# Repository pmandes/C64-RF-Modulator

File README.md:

# C64-RF-Modulator with S-Video Mod

This is a project of a modulator replacement based on an analog c0pperdragon module. It was adjusted in size to the Commodore C64C motherboard and extended with S-Video and Strereo Audio outputs.

### Changelog:

1.2
- internal audio route to left and/or right channel
- ferrite beads to suppresses high-frequency electronic noise
- silkscreen layer with descriptions of all outputs and elements
- 3D models for a nice rendering
- project cleaned up and migrated to KiCad 6.0
- interactive BOM

1.1
- prototype fixes

1.0
- PCB size adjusted to C64C motherboards (ASSY No.250469)
- S-Video connector added (mini-DIN 4)
- added standard stereo audio mini-jack 3.5mm output

### Bill of materials:

<p align="center">

</p>

### Final revision:

- all jumpers removed: audio output from an external source (e.g. MixSID)
- all jumpers on: mono signal from the motherboard connected to the left and right channels

### Prototype images:

The board connected to SixtyClone. Image from S-Video output:

The board can be soldered with pins to the motherboard. Then the S-Video and Audio outputs will be at the level of the corresponding openings in the housing.

### Links:
- c0pperdragon analog module: https://github.com/c0pperdragon/C64-Video-Enhancement/tree/master/analog_only
- order PCBs directly from PCBWay: https://www.pcbway.com/project/shareproject/Commodore_C64C_modulator_replacement_0f6cacf9.html

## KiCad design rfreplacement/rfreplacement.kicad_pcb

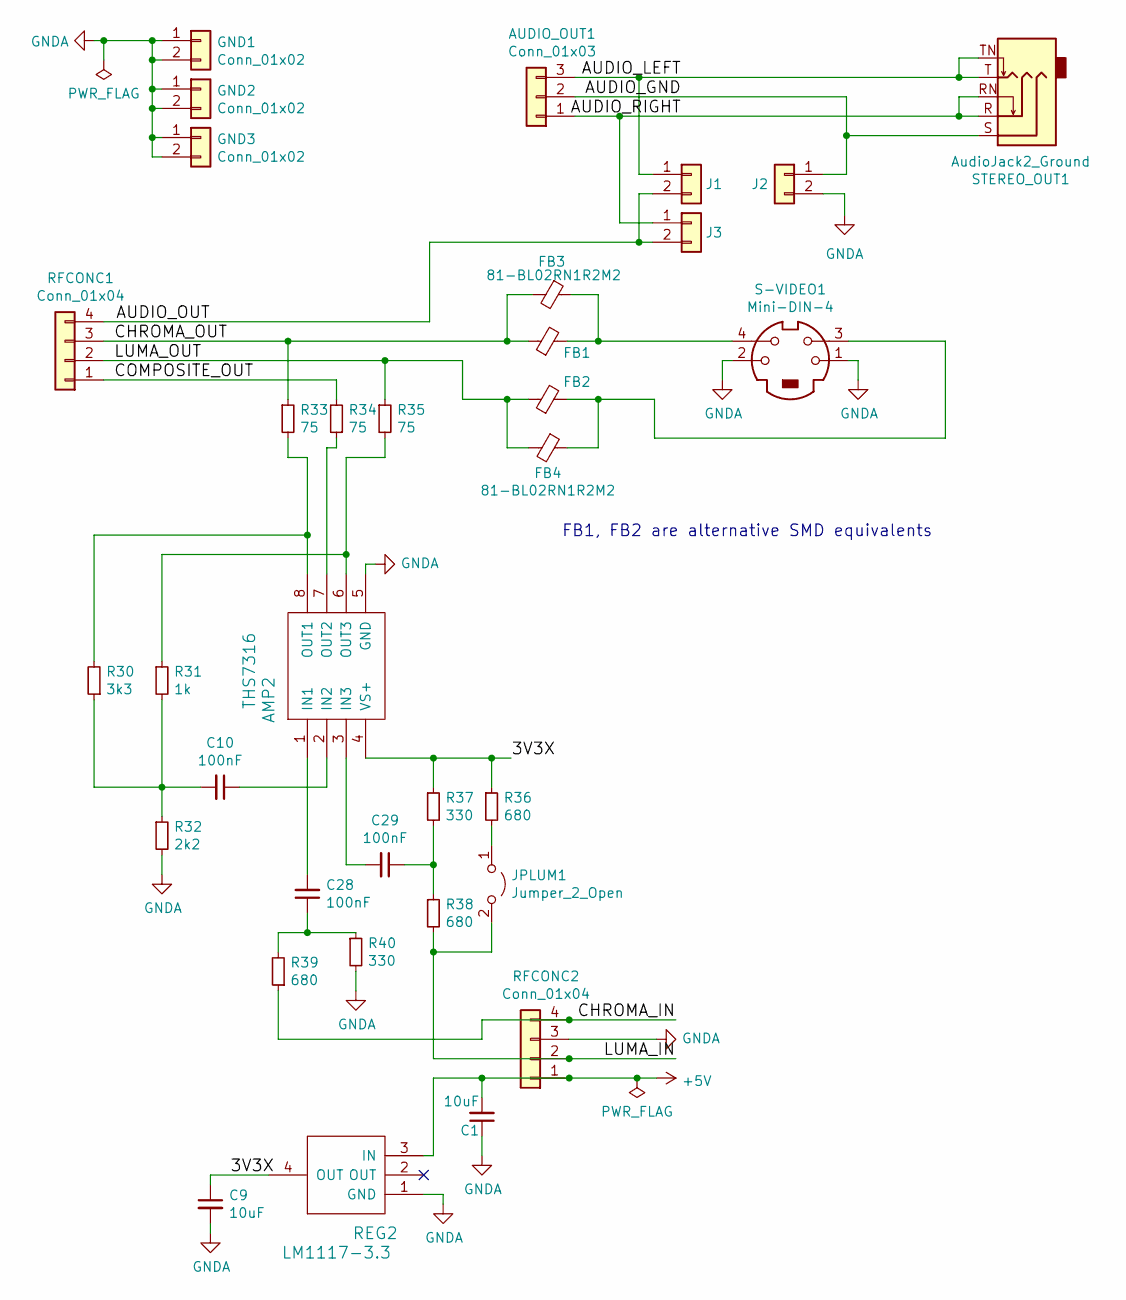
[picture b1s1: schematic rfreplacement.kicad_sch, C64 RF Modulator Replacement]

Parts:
AMP2: THS7316; SSOP-8_3.95x5.21x3.27mm_P1.27mm
AUDIO_OUT1: Conn_01x03; PinHeader_1x03_P2.54mm_Horizontal
C1, C9: 10uF; C_0805_2012Metric_Pad1.18x1.45mm_HandSolder
C10, C28, C29: 100nF; C_0805_2012Metric_Pad1.18x1.45mm_HandSolder
FB1, FB2: Ferrite Bead; L_0805_2012Metric_Pad1.15x1.40mm_HandSolder
FB3, FB4: 81-BL02RN1R2M2; R_Axial_DIN0207_L6.3mm_D2.5mm_P7.62mm_Horizontal
GND1, GND2, GND3: Conn_01x02; PinHeader_1x02_P2.54mm_Vertical
J1, J2, J3: Conn_01x02; PinHeader_1x02_P2.00mm_Vertical
JPLUM1: Jumper_2_Open; SolderJumper-2_P1.3mm_Open_RoundedPad1.0x1.5mm
R30: 3k3; R_0805_2012Metric_Pad1.15x1.40mm_HandSolder
R31: 1k; R_0805_2012Metric_Pad1.15x1.40mm_HandSolder
R32: 2k2; R_0805_2012Metric_Pad1.15x1.40mm_HandSolder
R33, R34, R35: 75; R_0805_2012Metric_Pad1.15x1.40mm_HandSolder
R36, R38, R39: 680; R_0805_2012Metric_Pad1.15x1.40mm_HandSolder
R37, R40: 330; R_0805_2012Metric_Pad1.15x1.40mm_HandSolder
REG2: LM1117-3.3; SOT-223
RFCONC1, RFCONC2: Conn_01x04; PinHeader_1x04_P2.54mm_Vertical
S-VIDEO1: Mini-DIN-4; TE_5749181-1
STEREO_OUT1: AudioJack2_Ground; Jack_3.5mm_Ledino_KB3SPRS_Horizontal

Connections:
+5V: C1.2, REG2.3 (IN), RFCONC2.1; also elsewhere on the board
/3V3X: AMP2.4 (VS+), C9.1, R36.1, R37.1, REG2.4 (OUT); also elsewhere on the board
/AUDIO_GND: AUDIO_OUT1.2, J2.1, STEREO_OUT1.S
/AUDIO_LEFT: AUDIO_OUT1.3, J1.1, STEREO_OUT1.T, STEREO_OUT1.TN
/AUDIO_OUT: J1.2, J3.2, RFCONC1.4
/AUDIO_RIGHT: AUDIO_OUT1.1, J3.1, STEREO_OUT1.R, STEREO_OUT1.RN
/CHROMA_IN: R39.1, RFCONC2.4
/CHROMA_OUT: FB1.1, FB3.2, R33.1, RFCONC1.3
/COMPOSITE_OUT: R34.2, RFCONC1.1
/LUMA_IN: JPLUM1.2 (B), R38.2, RFCONC2.2
/LUMA_OUT: FB2.1, FB4.2, R35.1, RFCONC1.2
GNDA: AMP2.5 (GND), C1.1, C9.2, GND1.1, GND1.2, GND2.1, GND2.2, GND3.1, GND3.2, J2.2, R32.2, R40.2, REG2.1 (GND), RFCONC2.3, S-VIDEO1.1, S-VIDEO1.2; also elsewhere on the board
unnamed 12: AMP2.1 (IN1), C28.2; also elsewhere on the board
unnamed 13: AMP2.2 (IN2), C10.1; also elsewhere on the board
unnamed 14: AMP2.3 (IN3), C29.2; also elsewhere on the board
unnamed 15: AMP2.6 (OUT3), R31.1, R35.2; also elsewhere on the board
unnamed 16: AMP2.7 (OUT2), R34.1; also elsewhere on the board
unnamed 17: AMP2.8 (OUT1), R30.2, R33.2; also elsewhere on the board
unnamed: C10.2, R30.1, R31.2, R32.1
unnamed: C28.1, R39.2, R40.1
unnamed: C29.1, R37.2, R38.1
unnamed: FB1.2, FB3.1, S-VIDEO1.4
unnamed: FB2.2, FB4.1, S-VIDEO1.3
unnamed: JPLUM1.1 (A), R36.2

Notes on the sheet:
FB1, FB2 are alternative SMD equivalents

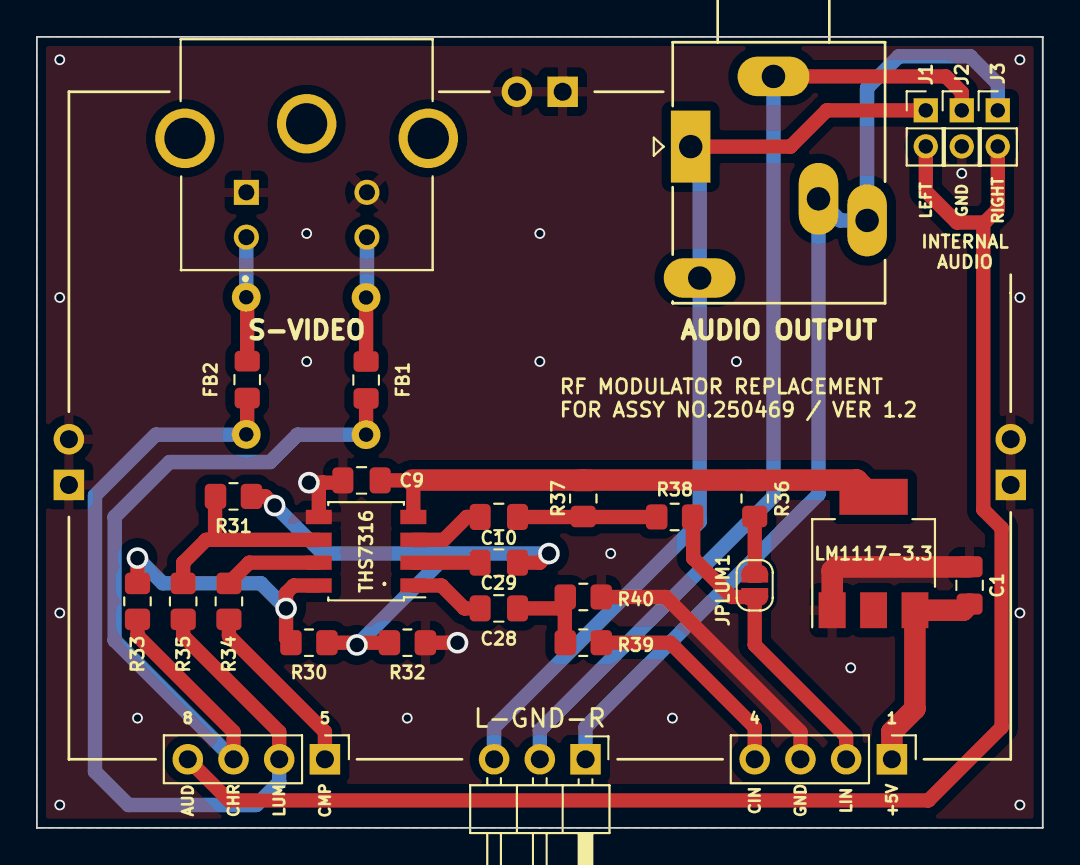
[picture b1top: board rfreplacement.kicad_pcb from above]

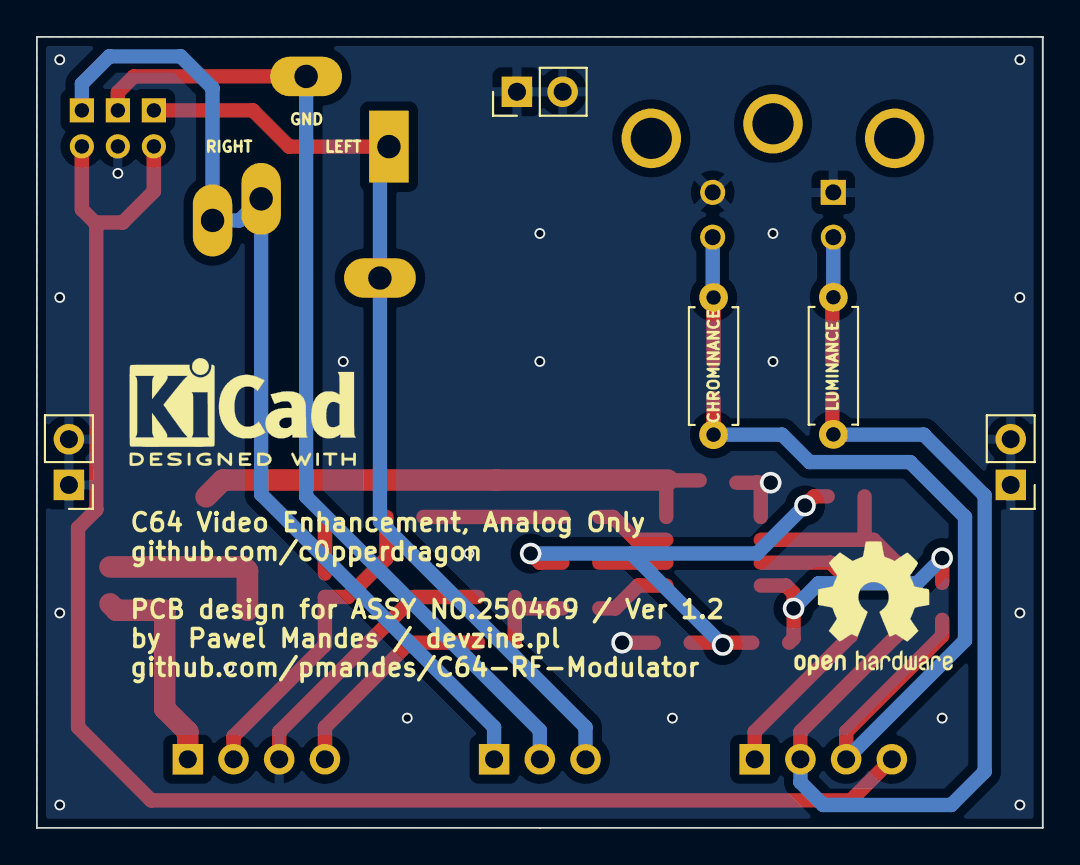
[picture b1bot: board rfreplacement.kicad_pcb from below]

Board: 2 copper layers, 55.9 x 43.9 mm, 34 parts (5 on the bottom side), 24 nets.

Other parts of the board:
LM1117-3.3: LM1117-3.3; SOT-223
THS7316: THS7316; SSOP-8_3.95x5.21x3.27mm_P1.27mm

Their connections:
+5V: LM1117-3.3.3 (IN); also elsewhere on the board
/3V3X: LM1117-3.3.4 (OUT), THS7316.4 (VS+); also elsewhere on the board
GNDA: LM1117-3.3.1 (GND), THS7316.5 (GND); also elsewhere on the board
unnamed 12: THS7316.1 (IN1); also elsewhere on the board
unnamed 13: THS7316.2 (IN2); also elsewhere on the board
unnamed 14: THS7316.3 (IN3); also elsewhere on the board
unnamed 15: THS7316.6 (OUT3); also elsewhere on the board
unnamed 16: THS7316.7 (OUT2); also elsewhere on the board
unnamed 17: THS7316.8 (OUT1); also elsewhere on the board

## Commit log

2021-02-28 Breadbin connectors removed, S-Video/Stereo Audio output connectors added, new PCB layout for C64C motherboards.
2021-02-28 Pinheaders moved to the bottom side.
2021-03-03 Layout cleanup.
2021-03-04 PCB labels cleanup.
2021-03-05 Gerber files added.
2021-03-09 Dimensions adjusted.
2021-03-15 Connectors position adjusted.
2021-03-15 New gerber files.
2022-02-21 PCB ver 1.2
2022-02-21 New gerber file
2022-02-21 Gerbers updated. Prototype images.
2022-03-23 Ver1.2 final. Interactive BOM.
